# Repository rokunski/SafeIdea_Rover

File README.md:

# SafeIdea_rover

Raspberry:
login: pi
password: 1234

to make cv_bridge working:
https://github.com/pulver22/gym-gazebo/wiki/ERROR:-Cv_bridge-for-Python3

sample python code in package rover_safeidea, file scenario_1.py

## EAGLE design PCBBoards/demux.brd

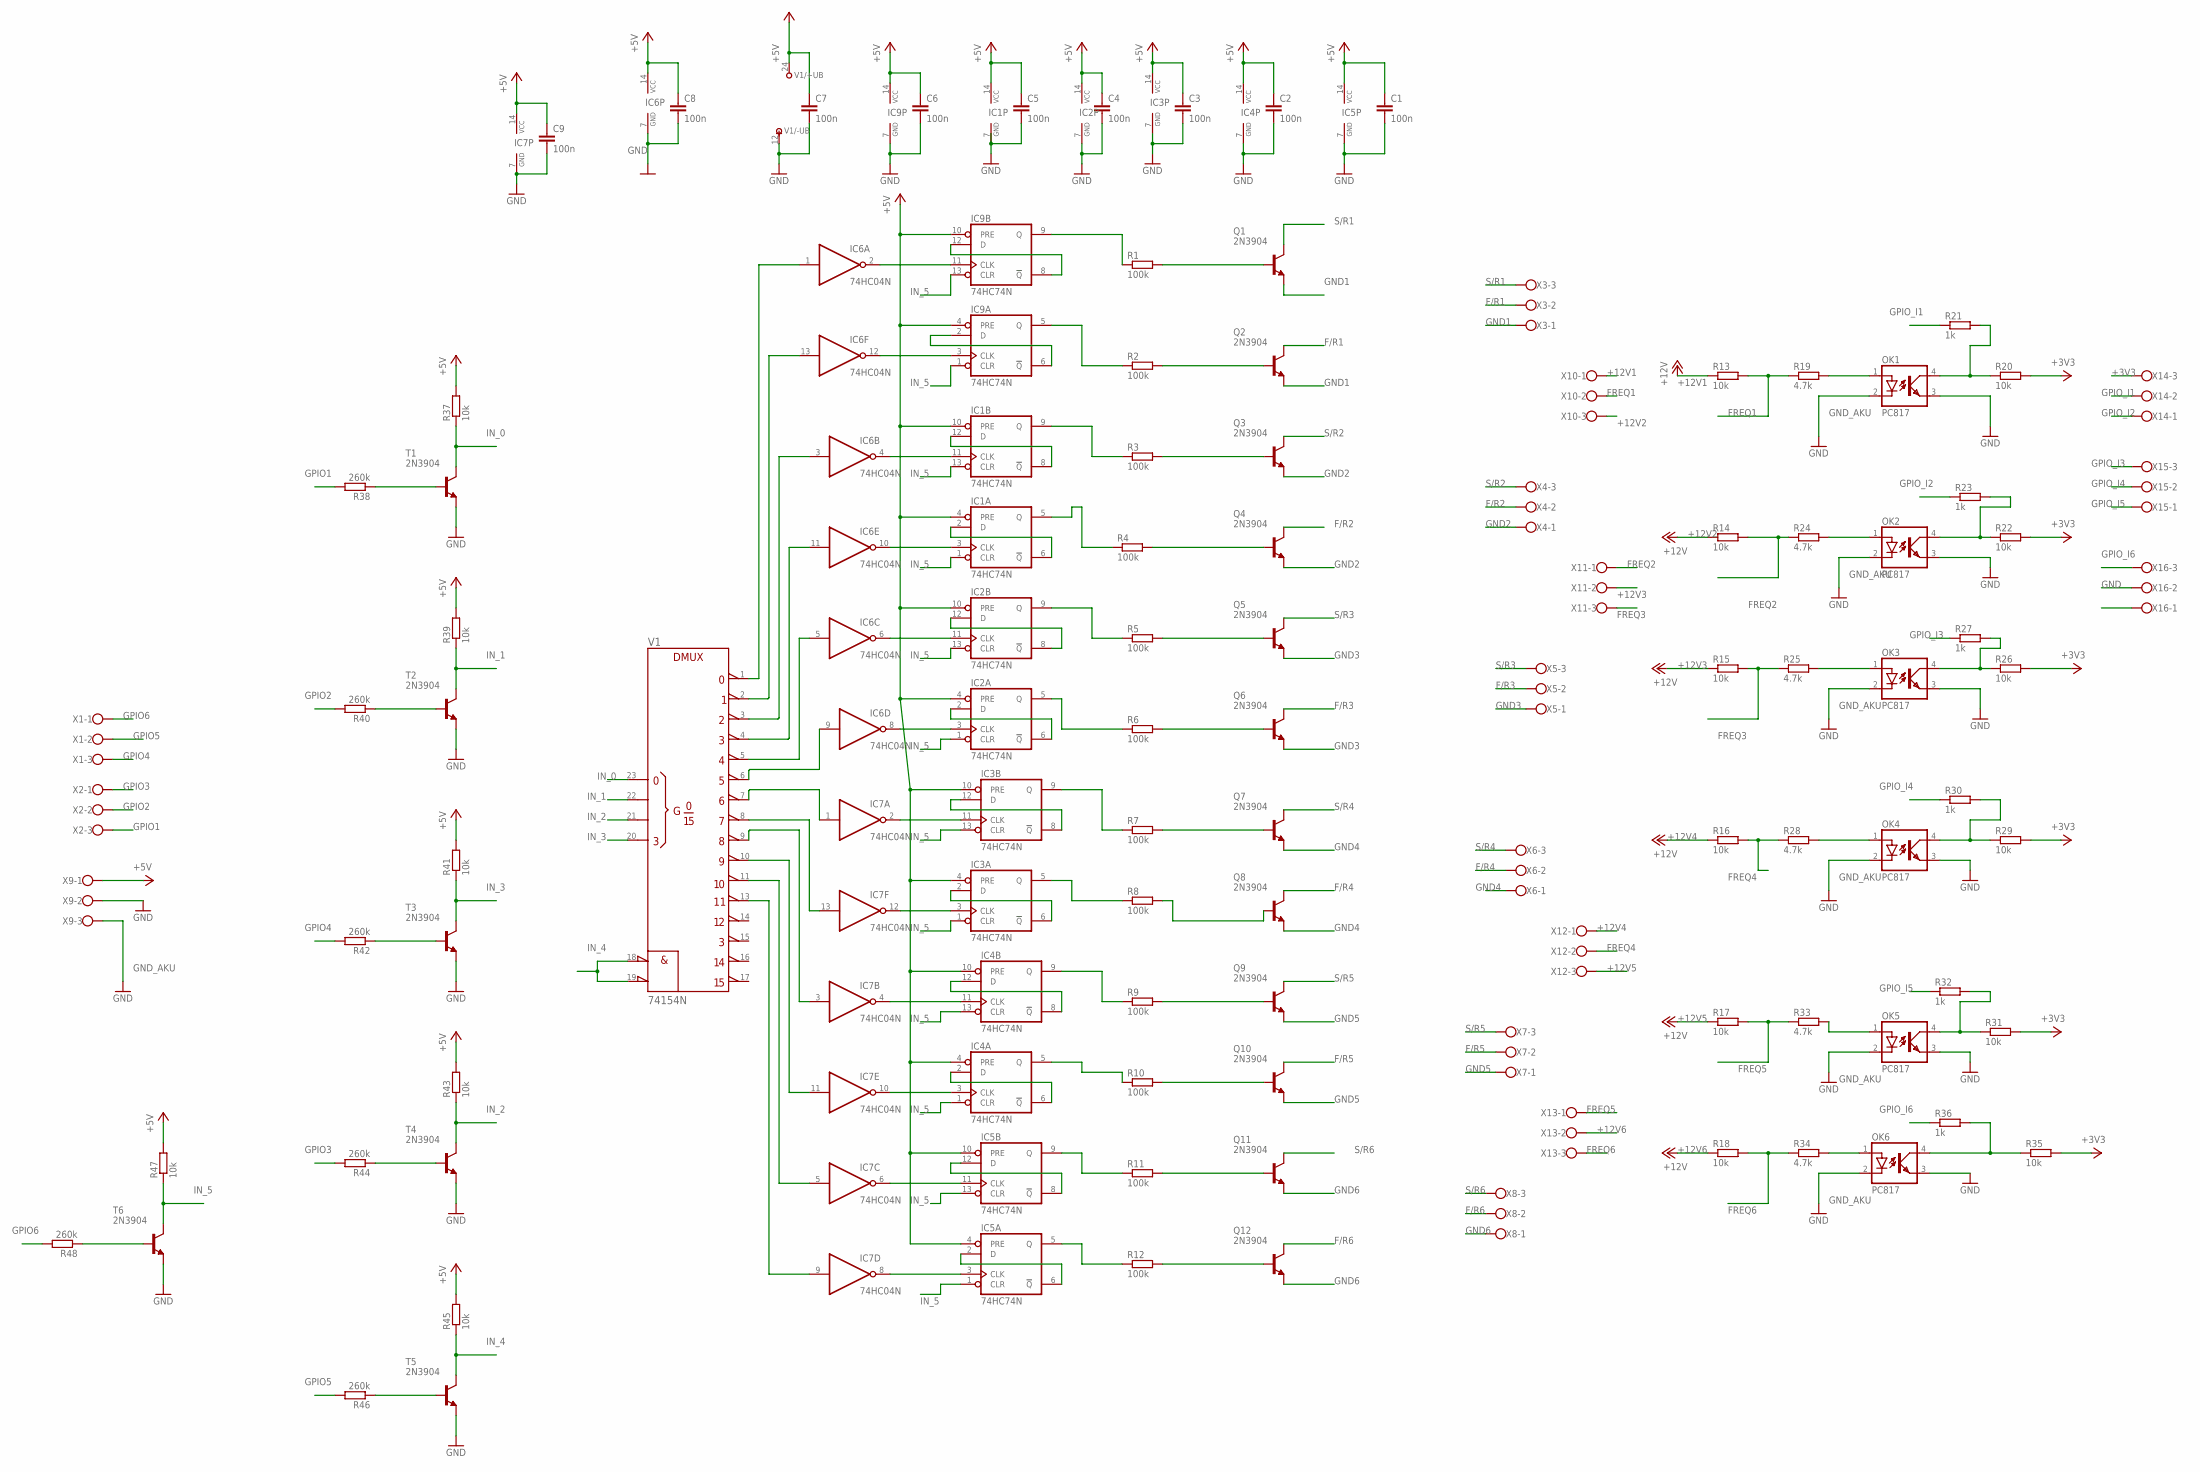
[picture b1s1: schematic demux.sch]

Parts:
C1, C2, C3, C4, C5, C6, C7, C8, C9: 100n; C025-025X050
IC1, IC2, IC3, IC4, IC5, IC9: 74HC74N; DIL14
IC6, IC7: 74HC04N; DIL14
OK1, OK2, OK3, OK4, OK5, OK6: PC817; DIL04
Q1, Q2, Q3, Q4, Q5, Q6, Q7, Q8, Q9, Q10, Q11, Q12: 2N3904; TO92
R1, R2, R3, R4, R5, R6, R7, R8, R9, R10, R11, R12: 100k; 0309/12
R13, R14, R15, R16, R17, R18: 10k; 0309/12
R19, R24, R25, R28, R33, R34: 4.7k; 0207/12
R20, R22, R26, R29, R31, R35: 10k; 0207/12
R21, R23, R27, R30, R32, R36: 1k; 0207/12
R37, R39, R41, R43, R45, R47: 10k; 0207/10
R38, R40, R42, R44, R46, R48: 260k; 0207/10
T1, T2, T3, T4, T5, T6: 2N3904; TO92
V1: 74154N; DIL24-3
X1, X2, X3, X4, X5, X6, X7, X8, X9, X10, X11, X12, X13, X14, X15, X16: W237-103

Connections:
+3V3: R20.2, R22.2, R26.2, R29.2, R31.2, R35.2, X14.3
+5V: C1.1, C2.1, C3.1, C4.1, C5.1, C6.1, C7.1, C8.1, C9.1, IC1.4 (PRE), IC1.10 (PRE), IC1.14 (VCC), IC2.4 (PRE), IC2.10 (PRE), IC2.14 (VCC), IC3.4 (PRE), IC3.10 (PRE), IC3.14 (VCC), IC4.4 (PRE), IC4.10 (PRE), IC4.14 (VCC), IC5.4 (PRE), IC5.10 (PRE), IC5.14 (VCC), IC6.14 (VCC), IC7.14 (VCC), IC9.4 (PRE), IC9.10 (PRE), IC9.14 (VCC), R37.2, R39.2, R41.2, R43.2, R45.2, R47.2, V1.24 (+UB), X9.1
+12V1: R13.1, X10.1
+12V2: R14.1, X10.3
+12V3: R15.1, X11.2
+12V4: R16.1, X12.1
+12V5: R17.1, X12.3
+12V6: R18.1, X13.2
F/R1: Q2.1 (C), X3.2
F/R2: Q4.1 (C), X4.2
F/R3: Q6.1 (C), X5.2
F/R4: Q8.1 (C), X6.2
F/R5: Q10.1 (C), X7.2
F/R6: Q12.1 (C), X8.2
FREQ1: R13.2, R19.1, X10.2
FREQ2: R14.2, R24.1, X11.1
FREQ3: R15.2, R25.1, X11.3
FREQ4: R16.2, R28.1, X12.2
FREQ5: R17.2, R33.1, X13.1
FREQ6: R18.2, R34.1, X13.3
GND: C1.2, C2.2, C3.2, C4.2, C5.2, C6.2, C7.2, C8.2, C9.2, IC1.7 (GND), IC2.7 (GND), IC3.7 (GND), IC4.7 (GND), IC5.7 (GND), IC6.7 (GND), IC7.7 (GND), IC9.7 (GND), OK1.3 (EMIT), OK2.3 (EMIT), OK3.3 (EMIT), OK4.3 (EMIT), OK5.3 (EMIT), OK6.3 (EMIT), T1.3 (E), T2.3 (E), T3.3 (E), T4.3 (E), T5.3 (E), T6.3 (E), V1.12 (-UB), X9.2, X16.2
GND1: Q1.3 (E), Q2.3 (E), X3.1
GND2: Q3.3 (E), Q4.3 (E), X4.1
GND3: Q5.3 (E), Q6.3 (E), X5.1
GND4: Q7.3 (E), Q8.3 (E), X6.1
GND5: Q9.3 (E), Q10.3 (E), X7.1
GND6: Q11.3 (E), Q12.3 (E), X8.1
GND_AKU: OK1.2 (C), OK2.2 (C), OK3.2 (C), OK4.2 (C), OK5.2 (C), OK6.2 (C), X9.3
GPIO1: R38.2, X2.3
GPIO2: R40.2, X2.2
GPIO3: R44.2, X2.1
GPIO4: R42.2, X1.3
GPIO5: R46.2, X1.2
GPIO6: R48.2, X1.1
GPIO_I1: R21.1, X14.2
GPIO_I2: R23.1, X14.1
GPIO_I3: R27.1, X15.3
GPIO_I4: R30.1, X15.2
GPIO_I5: R32.1, X15.1
GPIO_I6: R36.1, X16.3
IN_0: R37.1, T1.1 (C), V1.23 (A)
IN_1: R39.1, T2.1 (C), V1.22 (B)
IN_2: R43.1, T4.1 (C), V1.21 (C)
IN_3: R41.1, T3.1 (C), V1.20 (D)
IN_4: R45.1, T5.1 (C), V1.18 (!G1), V1.19 (!G2)
IN_5: IC1.1 (CLR), IC1.13 (CLR), IC2.1 (CLR), IC2.13 (CLR), IC3.1 (CLR), IC3.13 (CLR), IC4.1 (CLR), IC4.13 (CLR), IC5.1 (CLR), IC5.13 (CLR), IC9.1 (CLR), IC9.13 (CLR), R47.1, T6.1 (C)
unnamed: IC4.11 (CLK), IC7.4 (O)
unnamed: IC1.2 (D), IC1.6 (!Q)
unnamed: IC9.8 (!Q), IC9.12 (D)
unnamed: IC6.2 (O), IC9.11 (CLK)
unnamed: IC6.1 (I), V1.1 (0)
unnamed: IC3.8 (!Q), IC3.12 (D)
unnamed: IC3.2 (D), IC3.6 (!Q)
unnamed: IC2.8 (!Q), IC2.12 (D)
unnamed: IC5.2 (D), IC5.6 (!Q)
unnamed: IC7.11 (I), V1.10 (9)
unnamed: IC4.3 (CLK), IC7.10 (O)
unnamed: IC6.12 (O), IC9.3 (CLK)
unnamed: IC5.3 (CLK), IC7.8 (O)
unnamed: IC9.2 (D), IC9.6 (!Q)
unnamed: IC1.11 (CLK), IC6.4 (O)
unnamed: IC5.11 (CLK), IC7.6 (O)
unnamed: IC3.11 (CLK), IC7.2 (O)
unnamed: IC2.2 (D), IC2.6 (!Q)
unnamed: IC3.3 (CLK), IC7.12 (O)
unnamed: IC4.2 (D), IC4.6 (!Q)
unnamed: IC1.8 (!Q), IC1.12 (D)
unnamed: IC2.3 (CLK), IC6.8 (O)
unnamed: IC2.11 (CLK), IC6.6 (O)
unnamed: IC1.3 (CLK), IC6.10 (O)
unnamed: IC6.13 (I), V1.2 (1)
unnamed: IC6.3 (I), V1.3 (2)
unnamed: IC6.11 (I), V1.4 (3)
unnamed: IC6.5 (I), V1.5 (4)
unnamed: IC6.9 (I), V1.6 (5)
unnamed: IC7.1 (I), V1.7 (6)
unnamed: IC7.13 (I), V1.8 (7)
unnamed: IC4.8 (!Q), IC4.12 (D)
unnamed: IC5.8 (!Q), IC5.12 (D)
unnamed: IC7.5 (I), V1.11 (10)
unnamed: IC7.9 (I), V1.13 (11)
unnamed: IC9.9 (Q), R1.1
unnamed: Q1.2 (B), R1.2
unnamed: Q2.2 (B), R2.2
unnamed: IC9.5 (Q), R2.1
unnamed: IC1.9 (Q), R3.1
unnamed: Q3.2 (B), R3.2
unnamed: Q4.2 (B), R4.2
unnamed: IC1.5 (Q), R4.1
unnamed: IC2.9 (Q), R5.1
unnamed: Q5.2 (B), R5.2
unnamed: Q6.2 (B), R6.2
unnamed: IC2.5 (Q), R6.1
unnamed: IC3.9 (Q), R7.1
unnamed: Q7.2 (B), R7.2
unnamed: Q8.2 (B), R8.2
unnamed: IC3.5 (Q), R8.1
unnamed: IC4.9 (Q), R9.1
unnamed: Q9.2 (B), R9.2
unnamed: Q10.2 (B), R10.2
unnamed: IC4.5 (Q), R10.1
unnamed: IC5.9 (Q), R11.1
unnamed: Q11.2 (B), R11.2
unnamed: Q12.2 (B), R12.2
unnamed: IC5.5 (Q), R12.1
unnamed: OK1.1 (A), R19.2
unnamed: OK1.4 (COL), R20.1, R21.2
unnamed: R40.1, T2.2 (B)
unnamed: OK6.4 (COL), R35.1, R36.2
unnamed: OK5.4 (COL), R31.1, R32.2
unnamed: OK4.4 (COL), R29.1, R30.2
unnamed: OK3.4 (COL), R26.1, R27.2
unnamed: OK2.4 (COL), R22.1, R23.2
unnamed: OK2.1 (A), R24.2
unnamed: R38.1, T1.2 (B)
unnamed: OK3.1 (A), R25.2
unnamed: R42.1, T3.2 (B)
unnamed: OK4.1 (A), R28.2
unnamed: R44.1, T4.2 (B)
unnamed: OK5.1 (A), R33.2
unnamed: R46.1, T5.2 (B)
unnamed: OK6.1 (A), R34.2
unnamed: R48.1, T6.2 (B)
unnamed: IC7.3 (I), V1.9 (8)
S/R1: Q1.1 (C), X3.3
S/R2: Q3.1 (C), X4.3
S/R3: Q5.1 (C), X5.3
S/R4: Q7.1 (C), X6.3
S/R5: Q9.1 (C), X7.3
S/R6: Q11.1 (C), X8.3

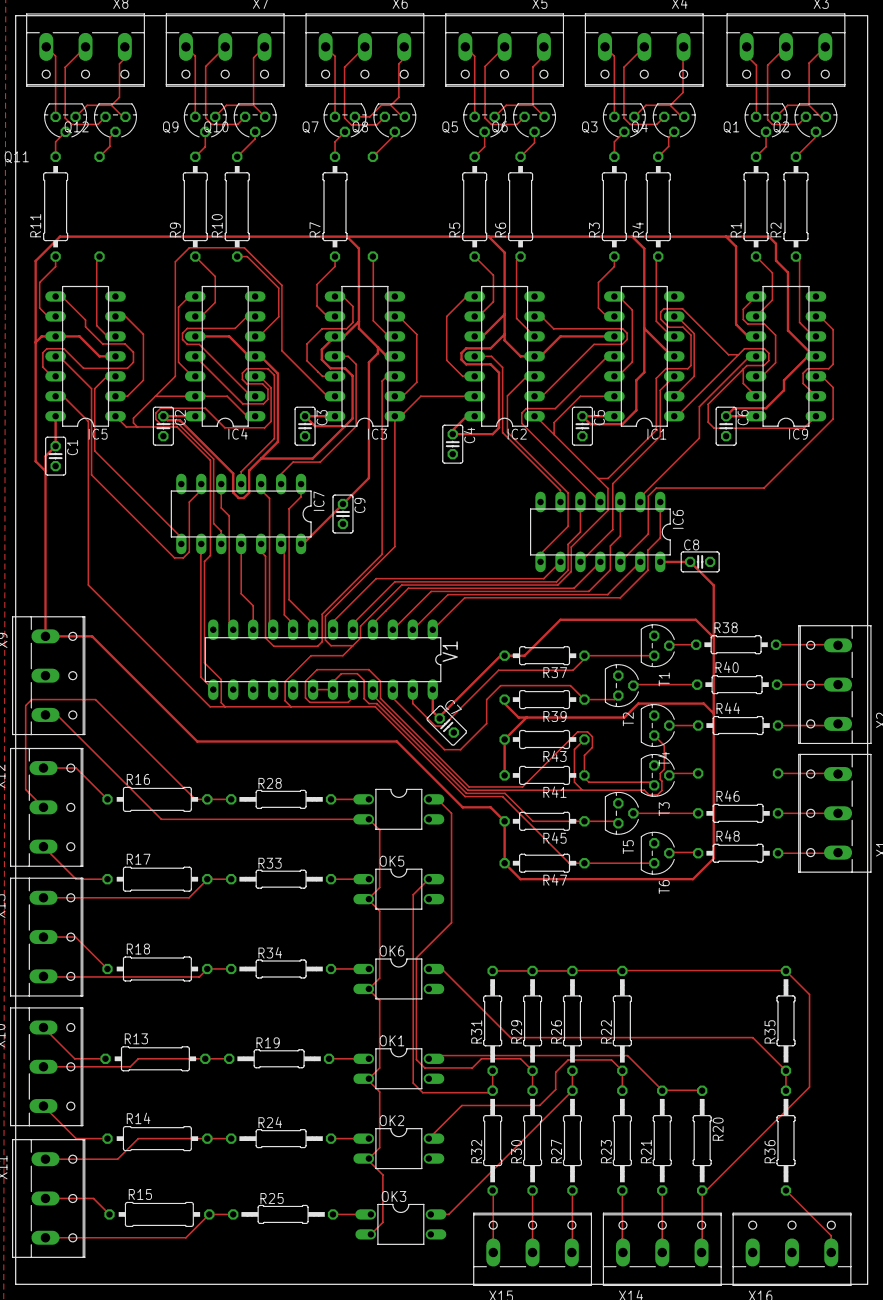
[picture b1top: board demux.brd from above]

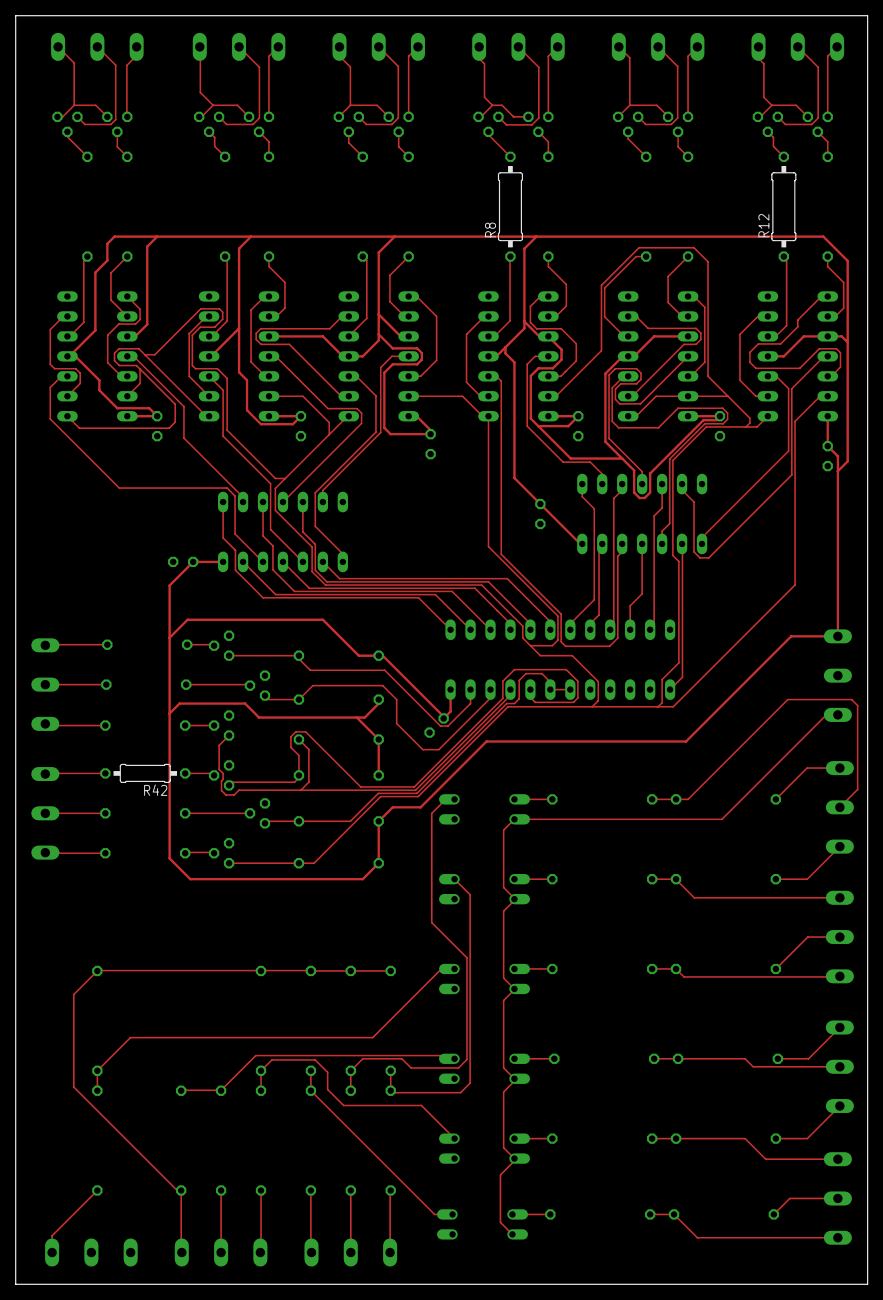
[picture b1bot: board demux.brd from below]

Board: 2 copper layers, 108.4 x 161.5 mm, 106 parts (3 on the bottom side), 130 nets.

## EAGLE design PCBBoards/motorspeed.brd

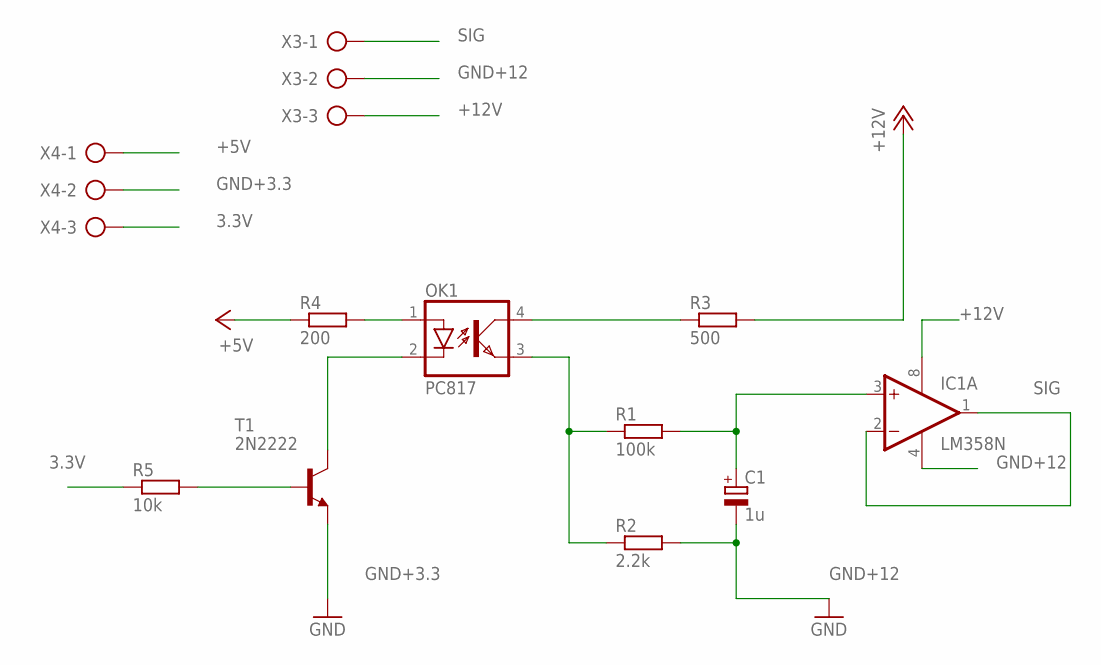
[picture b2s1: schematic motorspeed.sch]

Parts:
C1: 1u; E2-5
IC1: LM358N; DIL08
OK1: PC817; DIL04
R1: 100k; 0207/12
R2: 2.2k; 0207/12
R3: 500; 0207/12
R4: 200; 0207/12
R5: 10k; 0207/12
T1: 2N2222; TO18
X3, X4: AK500/3-H

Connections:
3.3V: R5.1, X4.3
+5V: R4.1, X4.1
+12V: IC1.8 (V+), R3.2, X3.3
GND+3.3: T1.1 (E), X4.2
GND+12: C1.-, IC1.4 (V-), R2.2, X3.2
unnamed: OK1.4 (COL), R3.1
unnamed: OK1.3 (EMIT), R1.1, R2.1
unnamed: C1.+, IC1.3 (+IN), R1.2
unnamed: OK1.2 (C), T1.3 (C)
unnamed: R5.2, T1.2 (B)
unnamed: OK1.1 (A), R4.2
SIG: IC1.1 (OUT), IC1.2 (-IN), X3.1

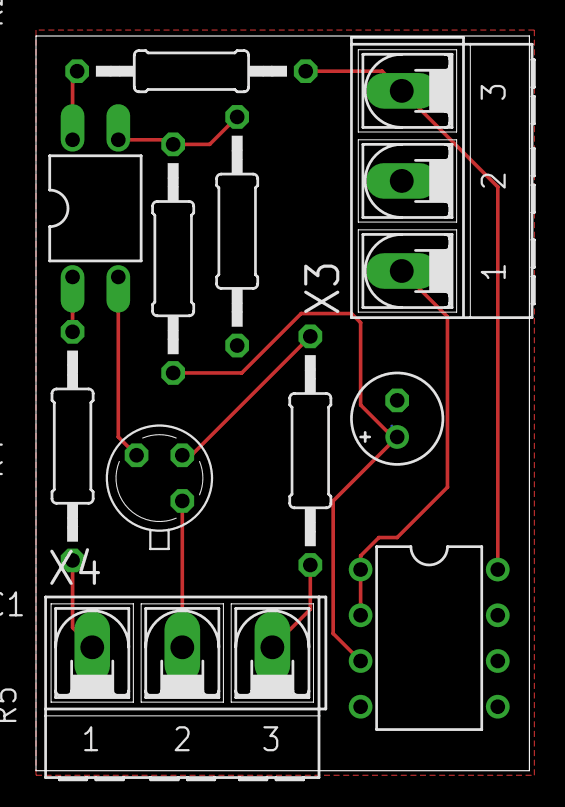
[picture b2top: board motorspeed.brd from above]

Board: 2 copper layers, 27.4 x 40.8 mm, 11 parts (0 on the bottom side), 12 nets.

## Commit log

2019-09-16 Add gitignore file
2019-09-16 Add curcuit for motor speed control
2019-09-17 Upgrade schema
2019-09-17 Add diagram picture
2019-09-17 Add circuit for motor speed control
2019-09-18 Add PCB board for motor speed circuit
2019-09-19 Update PCB Board
2019-09-19 PCBBoard expenditures
2019-09-19 typo
2019-09-19 Add ROS package - read controller input
2019-09-20 Hotspot
    Make hotspot for notebook-raspberry connection
2019-09-20 small update
2019-09-20 Update hotspot.sh
    Check if it was installed
2019-09-20 Simple publisher with data from controller
2019-09-20 update hotspot file
2019-09-20 add simple subscriber
2019-09-25 Small improvement and bug fixes
2019-09-25 Add simple keyboard listener
2019-10-01 final version
2019-10-03 update and small fixes
2019-10-04 Add working demo of PWM & rasp_master
2019-10-06 small update of keyboard node
2019-10-08 add demux eagle diagram
2019-10-08 Add motor_node & modified rasp_master
2019-10-08 Update launching motor nodes
2019-10-15 fr/sr update
2019-10-16 Add needed elements
2019-10-17 nothing important
2019-10-20 fr/sr another one
2019-10-21 first version of complited FR/SR PCB board
2019-10-22 FR/RS Board one of final update
2019-10-22 final version of FR/RS board
    i think :)
2019-10-24 Add simple simulation package
2019-10-26 FR/SR updated to 74HC**
2019-10-28 update SR/FR board
2019-10-30 Add rover to simulation
2019-11-02 Add some sensors to rover
    #TODO: fix laser sensor
2019-11-05 Add working simulation
2019-11-07 Add working (I hope) control system
    it's needed to add working control of Rasp GPIO
2019-11-10 update rover model
2019-11-10 something
2019-11-10 better movement
2019-11-10 to check update
2019-11-10 new version
2019-11-10 not bouncing
2019-11-10 add missing sensors
2019-11-11 update with working cv_bridge
2019-11-16 Add first version of beacon scenario
2019-11-17 ball
2019-11-17 animation test
2019-11-17 working sphere
2019-11-17 final ball trajectory
2019-11-17 static ball follower
2019-11-17 beacon finder - no obstacle
2019-11-18 Wireless transmitter finder - add obstacle avoiding
2019-11-18 data generator for sensors
2019-11-18 generating data - not final one
2019-11-19 improve control system software
2019-11-19 final data generator
2019-11-21 final follower scenario
2019-11-21 Add rasp master (the correct one) - not final one
2019-11-21 Decision system - interrupts
2019-11-22 Follower scenario - little fix
2020-11-10 Sensoryka
    Tutaj mam biblioteki i programy które udało mi się zrobić do sterowania. Jak kiedyś będę miał chwilę to opiszę co tam jest i jak to podłączyć.
